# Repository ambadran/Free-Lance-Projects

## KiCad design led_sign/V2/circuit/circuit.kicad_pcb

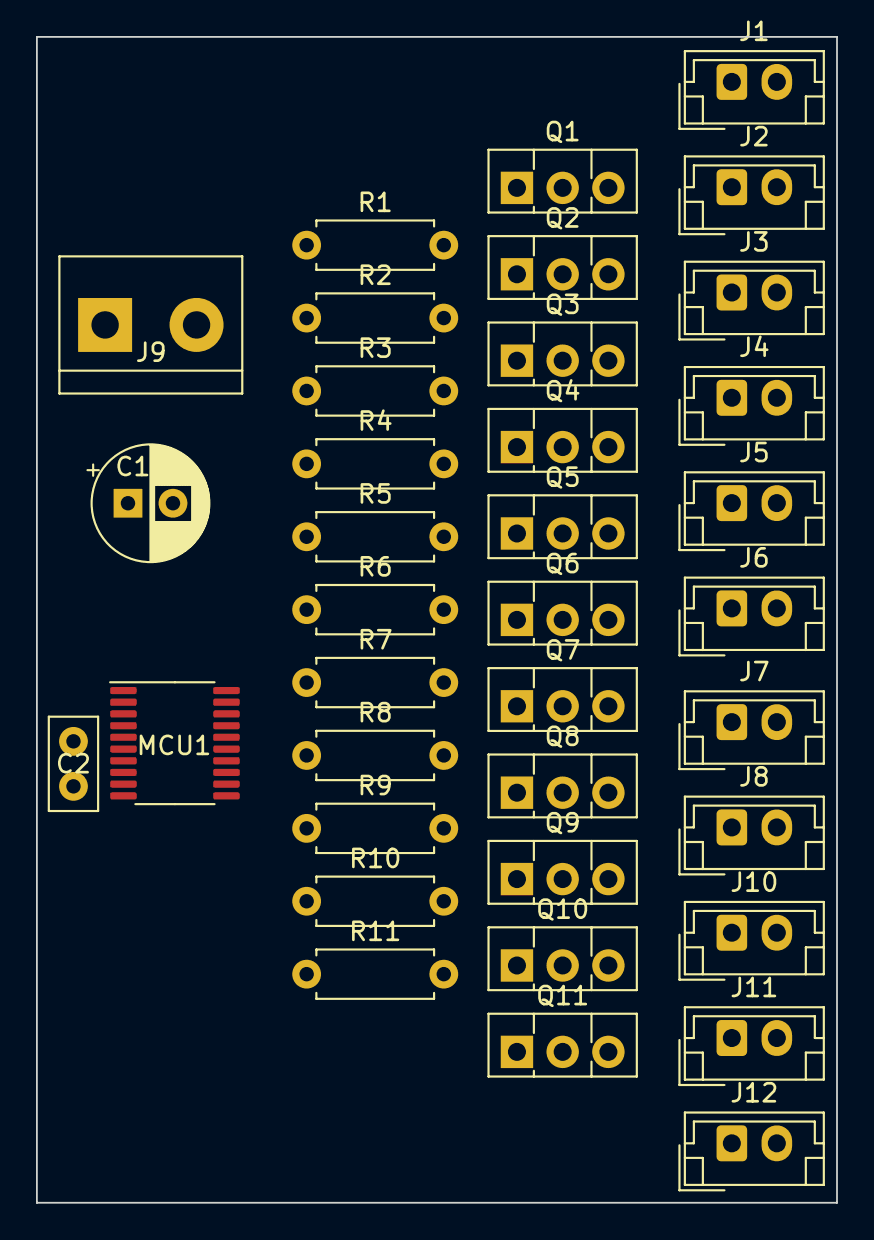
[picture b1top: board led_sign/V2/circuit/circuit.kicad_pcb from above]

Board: 2 copper layers, 44.5 x 64.8 mm, 37 parts (0 on the bottom side), 36 nets, no tracks yet.

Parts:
C1: 220uF; CP_Radial_D6.3mm_P2.50mm
C2: 10nF; C_Disc_D5.0mm_W2.5mm_P2.50mm
J1, J2, J3, J4, J5, J6, J7, J8, J10, J11, J12: JST2P; JST_EH_B2B-EH-A_1x02_P2.50mm_Vertical
J9: Terminal1x2; TerminalBlock_bornier-2_P5.08mm
MCU1: STC8G1k17; TSSOP-20_4.4x6.5mm_P0.65mm
Q1, Q2, Q3, Q4, Q5, Q6, Q7, Q8, Q9, Q10, Q11: Q_NPN_Darlington_BCE; TO-126-3_Vertical
R1, R2, R3, R4, R5, R6, R7, R8, R9, R10, R11: 330; R_Axial_DIN0207_L6.3mm_D2.5mm_P7.62mm_Horizontal

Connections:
+5V: C1.2, C2.1, MCU1.8, MCU1.9
+12V: J1.1, J2.1, J3.1, J4.1, J5.1, J6.1, J7.1, J8.1, J9.1, J10.1, J11.1, J12.1
GND: C1.1, C2.2, J9.2, MCU1.10, Q1.3 (E), Q2.3 (E), Q3.3 (E), Q4.3 (E), Q5.3 (E), Q6.3 (E), Q7.3 (E), Q8.3 (E), Q9.3 (E), Q10.3 (E), Q11.3 (E)
unnamed: J1.2, Q1.2 (C)
unnamed: J2.2, Q2.2 (C)
unnamed: J3.2, Q3.2 (C)
unnamed: J4.2, Q4.2 (C)
unnamed: J5.2, Q5.2 (C)
unnamed: J6.2, Q6.2 (C)
unnamed: J7.2, Q7.2 (C)
unnamed: J8.2, Q8.2 (C)
unnamed: J10.2, Q9.2 (C)
unnamed: J11.2, Q10.2 (C)
unnamed: J12.2, Q11.2 (C)
unnamed: Q1.1 (B), R1.2
unnamed: Q2.1 (B), R2.2
unnamed: Q3.1 (B), R3.2
unnamed: Q4.1 (B), R4.2
unnamed: Q5.1 (B), R5.2
unnamed: Q6.1 (B), R6.2
unnamed: Q7.1 (B), R7.2
unnamed: Q8.1 (B), R8.2
unnamed: Q9.1 (B), R9.2
unnamed: Q10.1 (B), R10.2
unnamed: Q11.1 (B), R11.2
Q1: MCU1.3, R1.1
Q2: MCU1.2, R2.1
Q3: MCU1.1, R3.1
Q4: MCU1.20, R4.1
Q5: MCU1.19, R5.1
Q6: MCU1.18, R6.1
Q7: MCU1.17, R7.1
Q8: MCU1.16, R8.1
Q9: MCU1.15, R9.1
Q10: MCU1.14, R10.1
Q11: MCU1.13, R11.1

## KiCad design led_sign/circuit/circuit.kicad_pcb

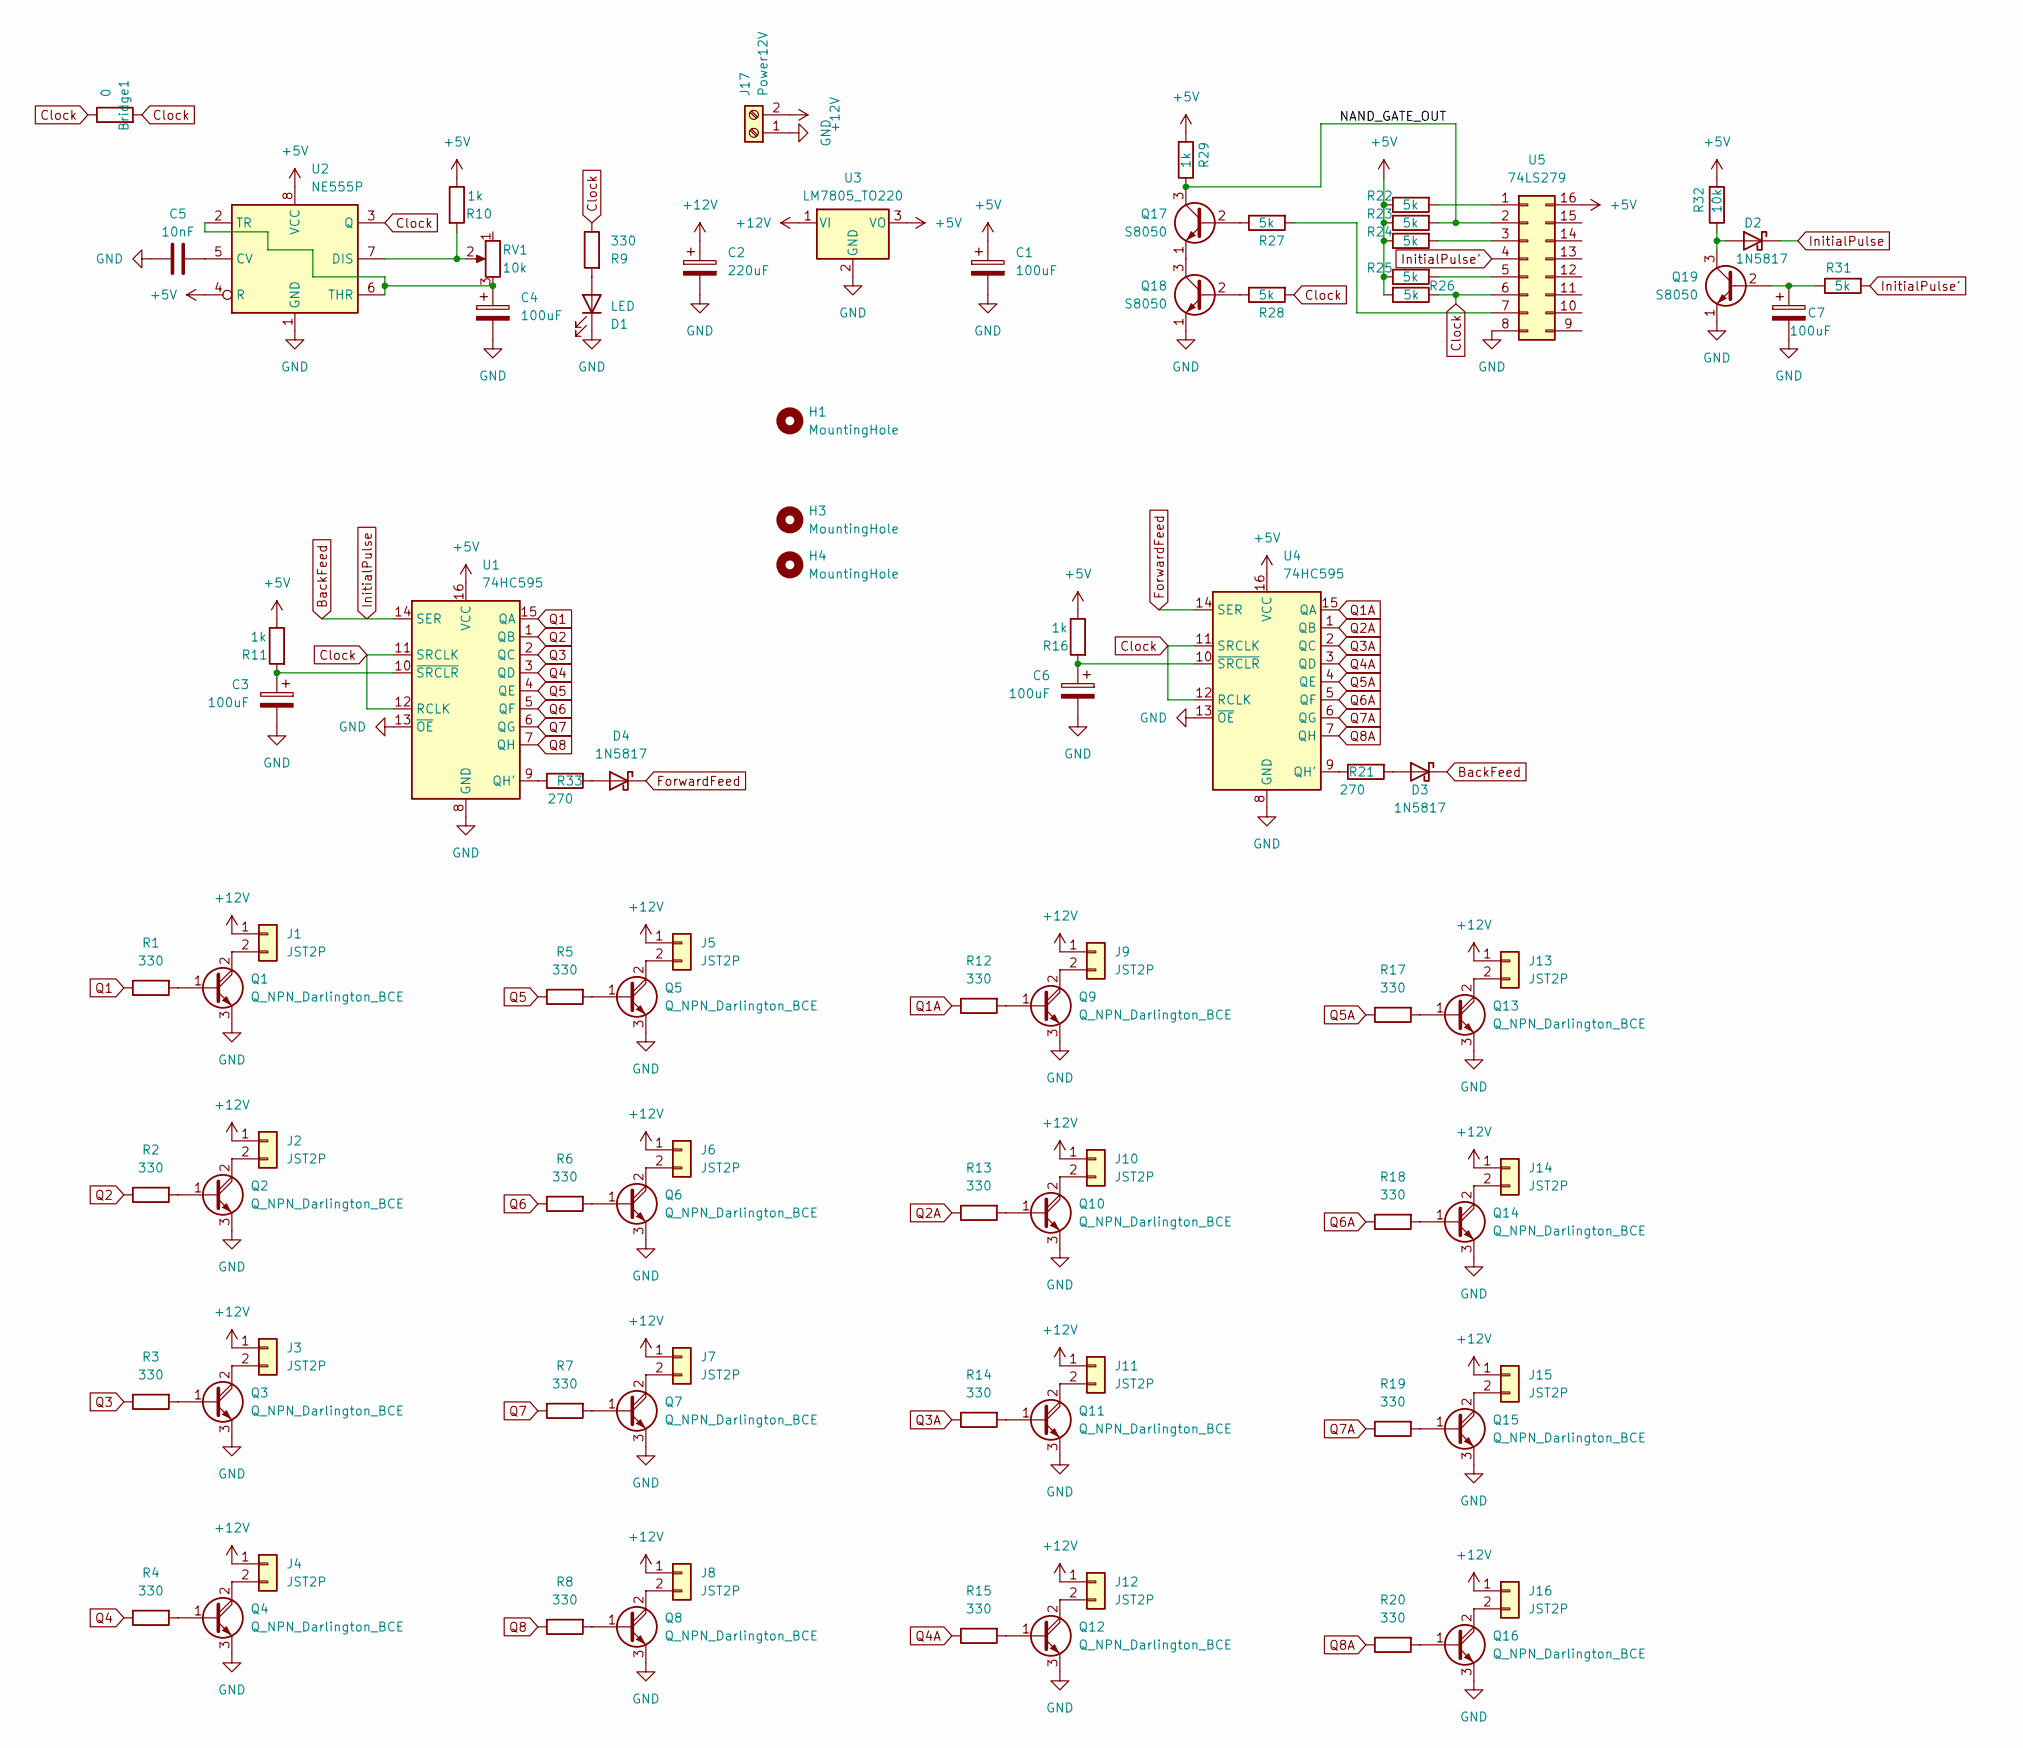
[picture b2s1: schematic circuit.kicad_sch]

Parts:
Bridge1: 0; R_Axial_DIN0207_L6.3mm_D2.5mm_P5.08mm_Vertical
C1, C3, C4, C6, C7: 100uF; CP_Radial_D5.0mm_P2.00mm
C2: 220uF; CP_Radial_D6.3mm_P2.50mm
C5: 10nF; C_Disc_D5.0mm_W2.5mm_P2.50mm
D1: LED; LED_D5.0mm
D2, D3, D4: 1N5817; D_DO-41_SOD81_P10.16mm_Horizontal
H1, H3, H4: MountingHole; MountingHole_3mm_Pad_TopBottom
J1, J2, J3, J4, J5, J6, J7, J8, J9, J10, J11, J12, J13, J14, J15, J16: JST2P; JST_EH_B2B-EH-A_1x02_P2.50mm_Vertical
J17: Power12V; TerminalBlock_bornier-2_P5.08mm
Q1, Q2, Q3, Q4, Q5, Q6, Q7, Q8, Q9, Q10, Q11, Q12, Q13, Q14, Q15, Q16: Q_NPN_Darlington_BCE; TO-126-3_Vertical
Q17, Q18, Q19: S8050; TO-92_Inline_Wide
R1, R2, R3, R4, R5, R6, R7, R8, R9, R12, R13, R14, R15, R17, R18, R19, R20: 330; R_Axial_DIN0207_L6.3mm_D2.5mm_P7.62mm_Horizontal
R10, R11, R16, R29: 1k; R_Axial_DIN0207_L6.3mm_D2.5mm_P7.62mm_Horizontal
R21, R33: 270; R_Axial_DIN0207_L6.3mm_D2.5mm_P7.62mm_Horizontal
R22, R23, R24, R25, R26, R27, R28, R31: 5k; R_Axial_DIN0207_L6.3mm_D2.5mm_P7.62mm_Horizontal
R32: 10k; R_Axial_DIN0207_L6.3mm_D2.5mm_P7.62mm_Horizontal
RV1: 10k; PinHeader_1x03_P2.54mm_Vertical
U1: 74HC595; DIP-16_W7.62mm_LongPads
U2: NE555P; DIP-8_W7.62mm
U3: LM7805_TO220; TO-220-3_Vertical
U4: 74HC595; DIP-16_W7.62mm_Socket_LongPads
U5: 74LS279; DIP-16_W7.62mm_Socket_LongPads

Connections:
+5V: C1.1, R10.1, R11.1, R16.1, R22.1, R23.1, R24.1, R25.1, R26.2, R29.2, R32.2, U1.16 (VCC), U2.4 (R), U2.8 (VCC), U3.3 (VO), U4.16 (VCC), U5.16
+12V: C2.1, J1.1, J2.1, J3.1, J4.1, J5.1, J6.1, J7.1, J8.1, J9.1, J10.1, J11.1, J12.1, J13.1, J14.1, J15.1, J16.1, J17.2, U3.1 (VI)
/NAND_GATE_OUT: Q17.3 (C), R23.2, R29.1, U5.2
BackFeed: D2.1 (K), D3.1 (K), U1.14 (SER)
Clock: Bridge1.1, Bridge1.2, R9.1, R26.1, R28.2, U1.11 (SRCLK), U1.12 (RCLK), U2.3 (Q), U4.11 (SRCLK), U4.12 (RCLK), U5.6
ForwardFeed: D4.1 (K), U4.14 (SER)
GND: C1.2, C2.2, C3.2, C4.2, C5.1, C6.2, C7.2, D1.1 (K), J17.1, Q1.3 (E), Q2.3 (E), Q3.3 (E), Q4.3 (E), Q5.3 (E), Q6.3 (E), Q7.3 (E), Q8.3 (E), Q9.3 (E), Q10.3 (E), Q11.3 (E), Q12.3 (E), Q13.3 (E), Q14.3 (E), Q15.3 (E), Q16.3 (E), Q18.1 (E), Q19.1 (E), U1.8 (GND), U1.13 (~OE), U2.1 (GND), U3.2 (GND), U4.8 (GND), U4.13 (~OE), U5.8
InitialPulse': R31.2, U5.4
unnamed: D1.2 (A), R9.2
unnamed: D2.2 (A), Q19.3 (C), R32.1
unnamed: D3.2 (A), R21.2
unnamed: D4.2 (A), R33.2
unnamed: J1.2, Q1.2 (C)
unnamed: J2.2, Q2.2 (C)
unnamed: J3.2, Q3.2 (C)
unnamed: J4.2, Q4.2 (C)
unnamed: J5.2, Q5.2 (C)
unnamed: J6.2, Q6.2 (C)
unnamed: J7.2, Q7.2 (C)
unnamed: J8.2, Q8.2 (C)
unnamed: J9.2, Q9.2 (C)
unnamed: J10.2, Q10.2 (C)
unnamed: J11.2, Q11.2 (C)
unnamed: J12.2, Q12.2 (C)
unnamed: J13.2, Q13.2 (C)
unnamed: J14.2, Q14.2 (C)
unnamed: J15.2, Q15.2 (C)
unnamed: J16.2, Q16.2 (C)
unnamed: Q1.1 (B), R1.2
unnamed: Q2.1 (B), R2.2
unnamed: Q3.1 (B), R3.2
unnamed: Q4.1 (B), R4.2
unnamed: Q5.1 (B), R5.2
unnamed: Q6.1 (B), R6.2
unnamed: Q7.1 (B), R7.2
unnamed: Q8.1 (B), R8.2
unnamed: Q9.1 (B), R12.2
unnamed: Q10.1 (B), R13.2
unnamed: Q11.1 (B), R14.2
unnamed: Q12.1 (B), R15.2
unnamed: Q13.1 (B), R17.2
unnamed: Q14.1 (B), R18.2
unnamed: Q15.1 (B), R19.2
unnamed: Q16.1 (B), R20.2
unnamed: Q17.2 (B), R27.1
unnamed: Q17.1 (E), Q18.3 (C)
unnamed: Q18.2 (B), R28.1
unnamed: C7.1, Q19.2 (B), R31.1
unnamed: R33.1, U1.9 (QH')
unnamed: C3.1, R11.2, U1.10 (~SRCLR)
unnamed: C5.2, U2.5 (CV)
unnamed: R10.2, RV1.2, U2.7 (DIS)
unnamed: C4.1, RV1.3, U2.2 (TR), U2.6 (THR)
unnamed: R21.1, U4.9 (QH')
unnamed: C6.1, R16.2, U4.10 (~SRCLR)
unnamed: R22.2, U5.1
unnamed: R24.2, U5.3
unnamed: R25.2, U5.5
unnamed: R27.2, U5.7
Q1: R1.1, U1.15 (QA)
Q1A: R12.1, U4.15 (QA)
Q2: R2.1, U1.1 (QB)
Q2A: R13.1, U4.1 (QB)
Q3: R3.1, U1.2 (QC)
Q3A: R14.1, U4.2 (QC)
Q4: R4.1, U1.3 (QD)
Q4A: R15.1, U4.3 (QD)
Q5: R5.1, U1.4 (QE)
Q5A: R17.1, U4.4 (QE)
Q6: R6.1, U1.5 (QF)
Q6A: R18.1, U4.5 (QF)
Q7: R7.1, U1.6 (QG)
Q7A: R19.1, U4.6 (QG)
Q8: R8.1, U1.7 (QH)
Q8A: R20.1, U4.7 (QH)

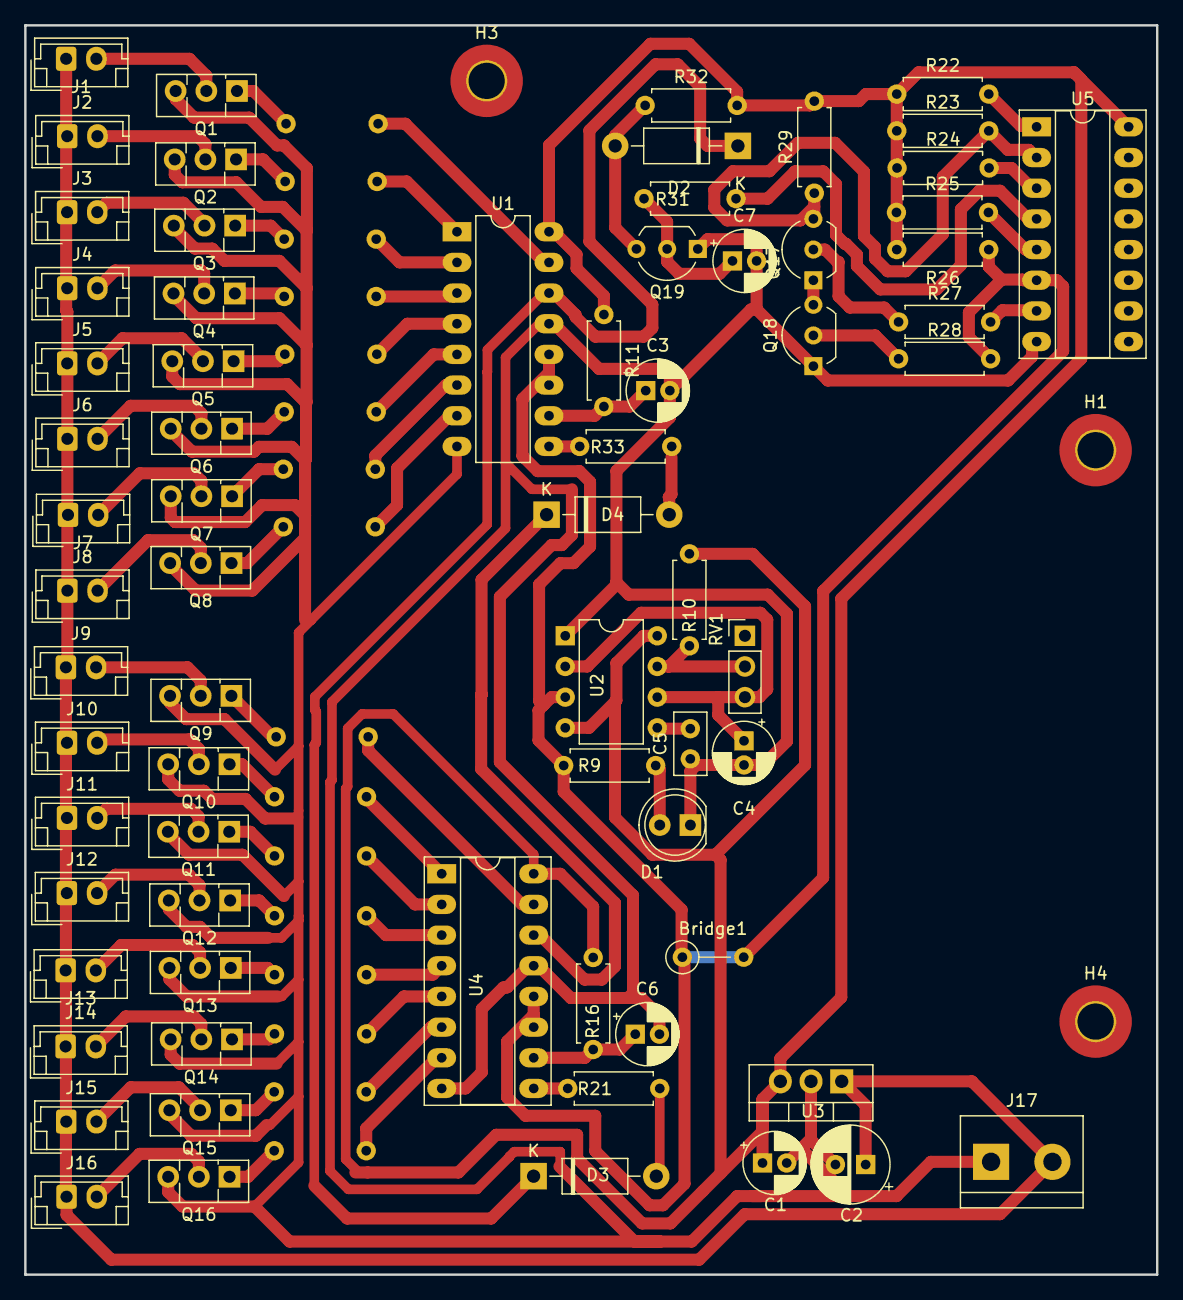
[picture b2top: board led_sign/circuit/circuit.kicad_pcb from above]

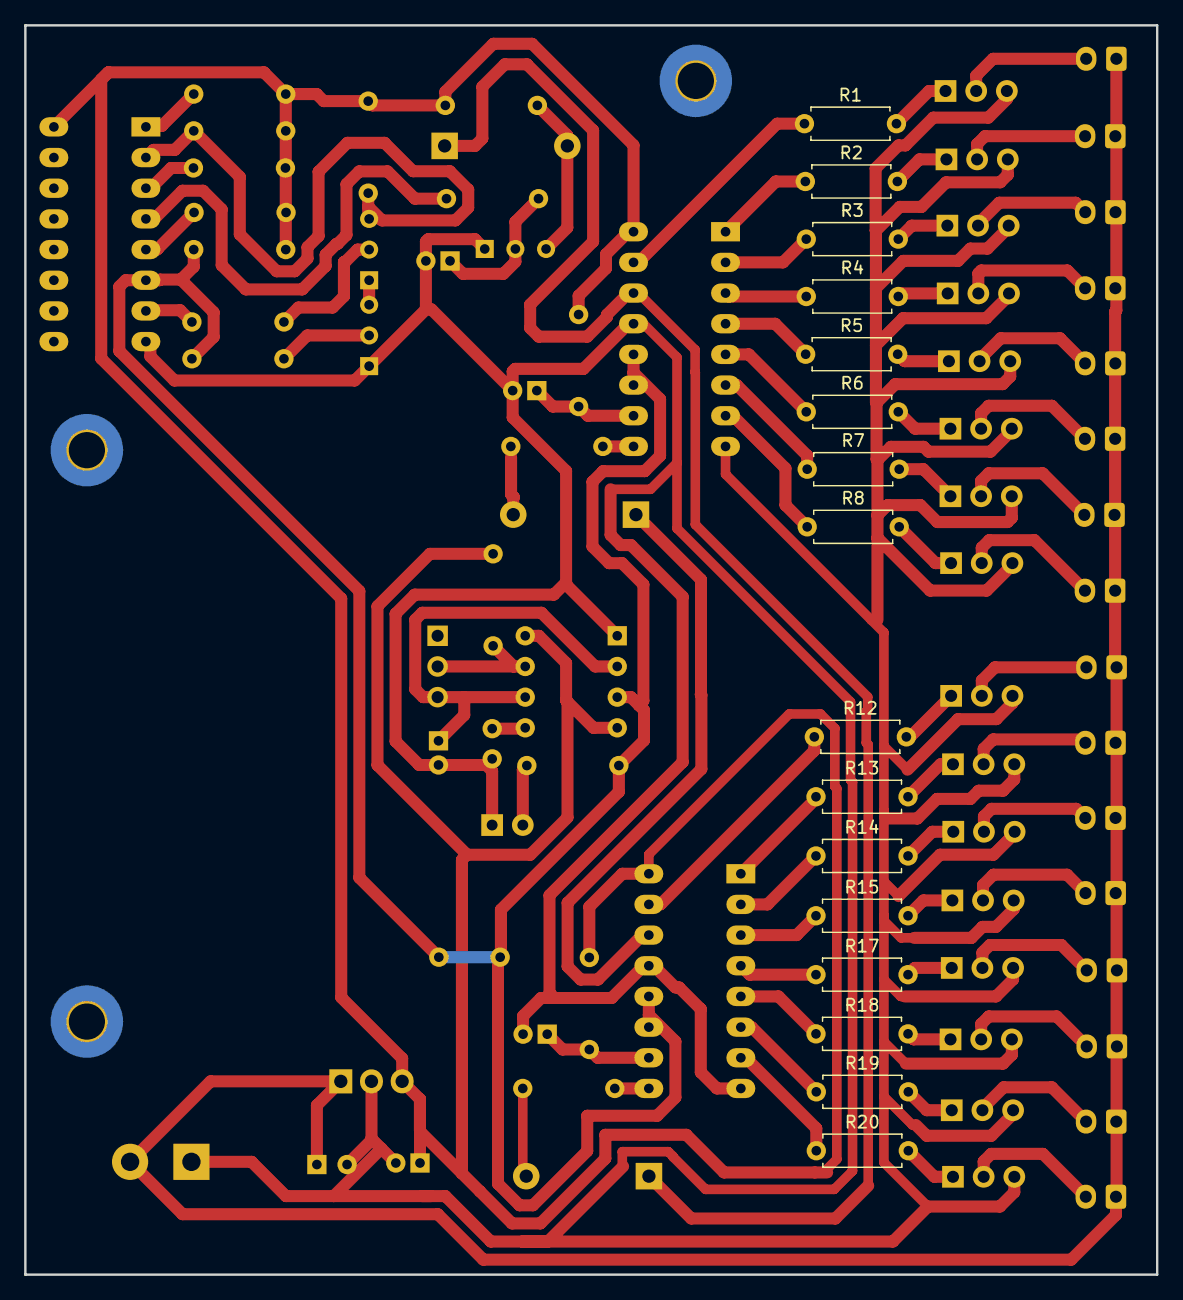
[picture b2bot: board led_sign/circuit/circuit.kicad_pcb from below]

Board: 2 copper layers, 93.7 x 103.5 mm, 89 parts (16 on the bottom side), 75 nets.

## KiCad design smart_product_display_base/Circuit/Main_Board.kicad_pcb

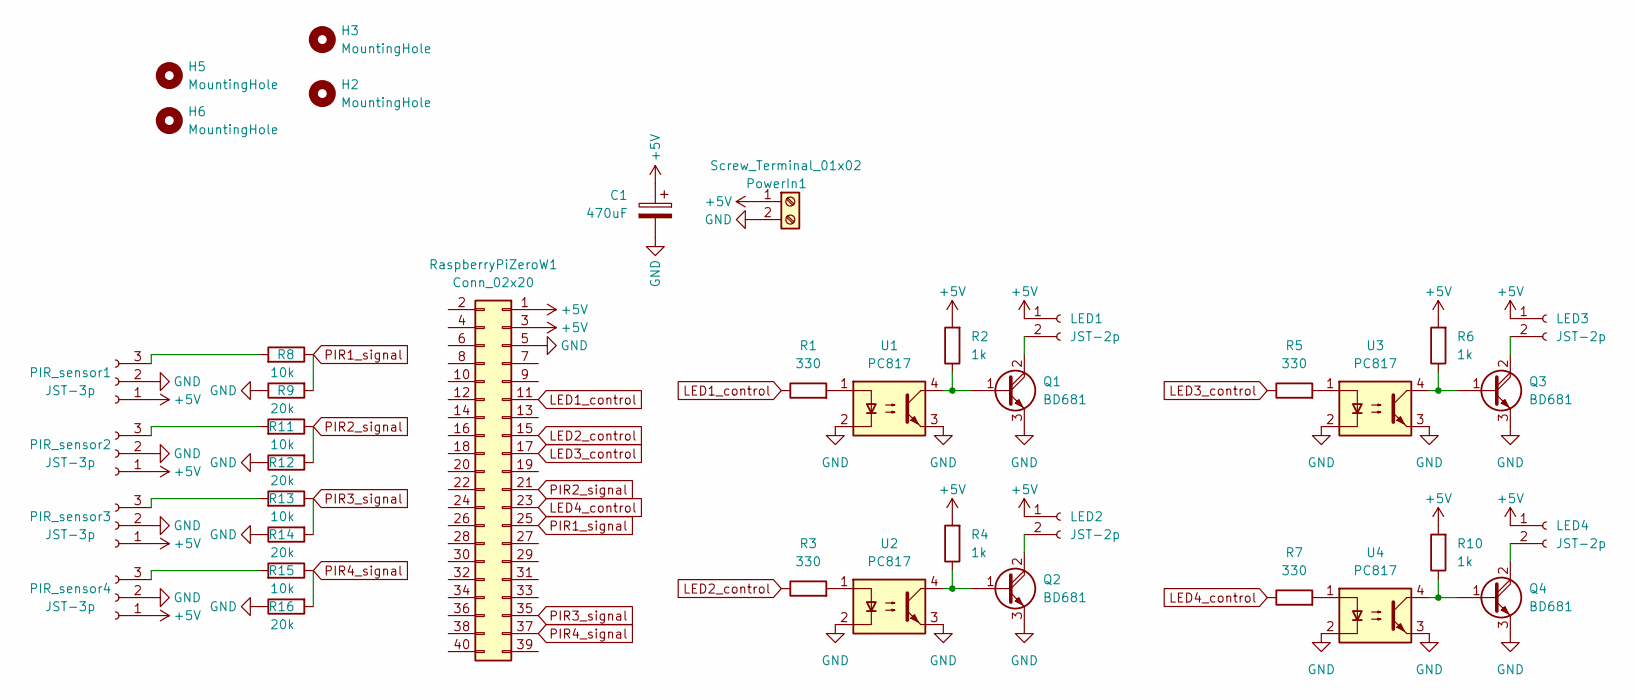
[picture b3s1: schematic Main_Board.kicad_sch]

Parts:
C1: 470uF; CP_Radial_D8.0mm_P3.50mm
H2, H3: MountingHole; MountingHole_4mm_Pad_TopOnly
H5, H6: MountingHole; MountingHole_2.5mm_Pad_TopOnly
LED1, LED2, LED3, LED4: JST-2p; JST_EH_B2B-EH-A_1x02_P2.50mm_Vertical
PIR_sensor1, PIR_sensor2, PIR_sensor3, PIR_sensor4: JST-3p; JST_EH_B3B-EH-A_1x03_P2.50mm_Vertical
PowerIn1: Screw_Terminal_01x02; TerminalBlock_bornier-2_P5.08mm
Q1, Q2, Q3, Q4: BD681; TO-126-3_Vertical
R1, R3, R5, R7: 330; R_Axial_DIN0207_L6.3mm_D2.5mm_P7.62mm_Horizontal
R2, R4, R6, R10: 1k; R_Axial_DIN0207_L6.3mm_D2.5mm_P7.62mm_Horizontal
R8, R11, R13, R15: 10k; R_Axial_DIN0207_L6.3mm_D2.5mm_P7.62mm_Horizontal
R9, R12, R14, R16: 20k; R_Axial_DIN0207_L6.3mm_D2.5mm_P7.62mm_Horizontal
RaspberryPiZeroW1: Conn_02x20; PinSocket_2x20_P2.54mm_Vertical
U1, U2, U3, U4: PC817; DIP-4_W7.62mm

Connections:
+5V: C1.1, LED1.1, LED2.1, LED3.1, LED4.1, PIR_sensor1.1, PIR_sensor2.1, PIR_sensor3.1, PIR_sensor4.1, PowerIn1.1, R2.2, R4.2, R6.2, R10.2, RaspberryPiZeroW1.1, RaspberryPiZeroW1.3
GND: C1.2, PIR_sensor1.2, PIR_sensor2.2, PIR_sensor3.2, PIR_sensor4.2, PowerIn1.2, Q1.3 (E), Q2.3 (E), Q3.3 (E), Q4.3 (E), R9.1, R12.1, R14.1, R16.1, RaspberryPiZeroW1.5, U1.2, U1.3, U2.2, U2.3, U3.2, U3.3, U4.2, U4.3
LED1_control: R1.1, RaspberryPiZeroW1.11
LED2_control: R3.1, RaspberryPiZeroW1.15
LED3_control: R5.1, RaspberryPiZeroW1.17
LED4_control: R7.1, RaspberryPiZeroW1.23
unnamed: LED1.2, Q1.2 (C)
unnamed: LED2.2, Q2.2 (C)
unnamed: LED3.2, Q3.2 (C)
unnamed: LED4.2, Q4.2 (C)
unnamed: PIR_sensor1.3, R8.2
unnamed: PIR_sensor2.3, R11.2
unnamed: PIR_sensor3.3, R13.2
unnamed: PIR_sensor4.3, R15.2
unnamed: Q1.1 (B), R2.1, U1.4
unnamed: Q2.1 (B), R4.1, U2.4
unnamed: Q3.1 (B), R6.1, U3.4
unnamed: Q4.1 (B), R10.1, U4.4
unnamed: R1.2, U1.1
unnamed: R3.2, U2.1
unnamed: R5.2, U3.1
unnamed: R7.2, U4.1
PIR1_signal: R8.1, R9.2, RaspberryPiZeroW1.25
PIR2_signal: R11.1, R12.2, RaspberryPiZeroW1.21
PIR3_signal: R13.1, R14.2, RaspberryPiZeroW1.35
PIR4_signal: R15.1, R16.2, RaspberryPiZeroW1.37

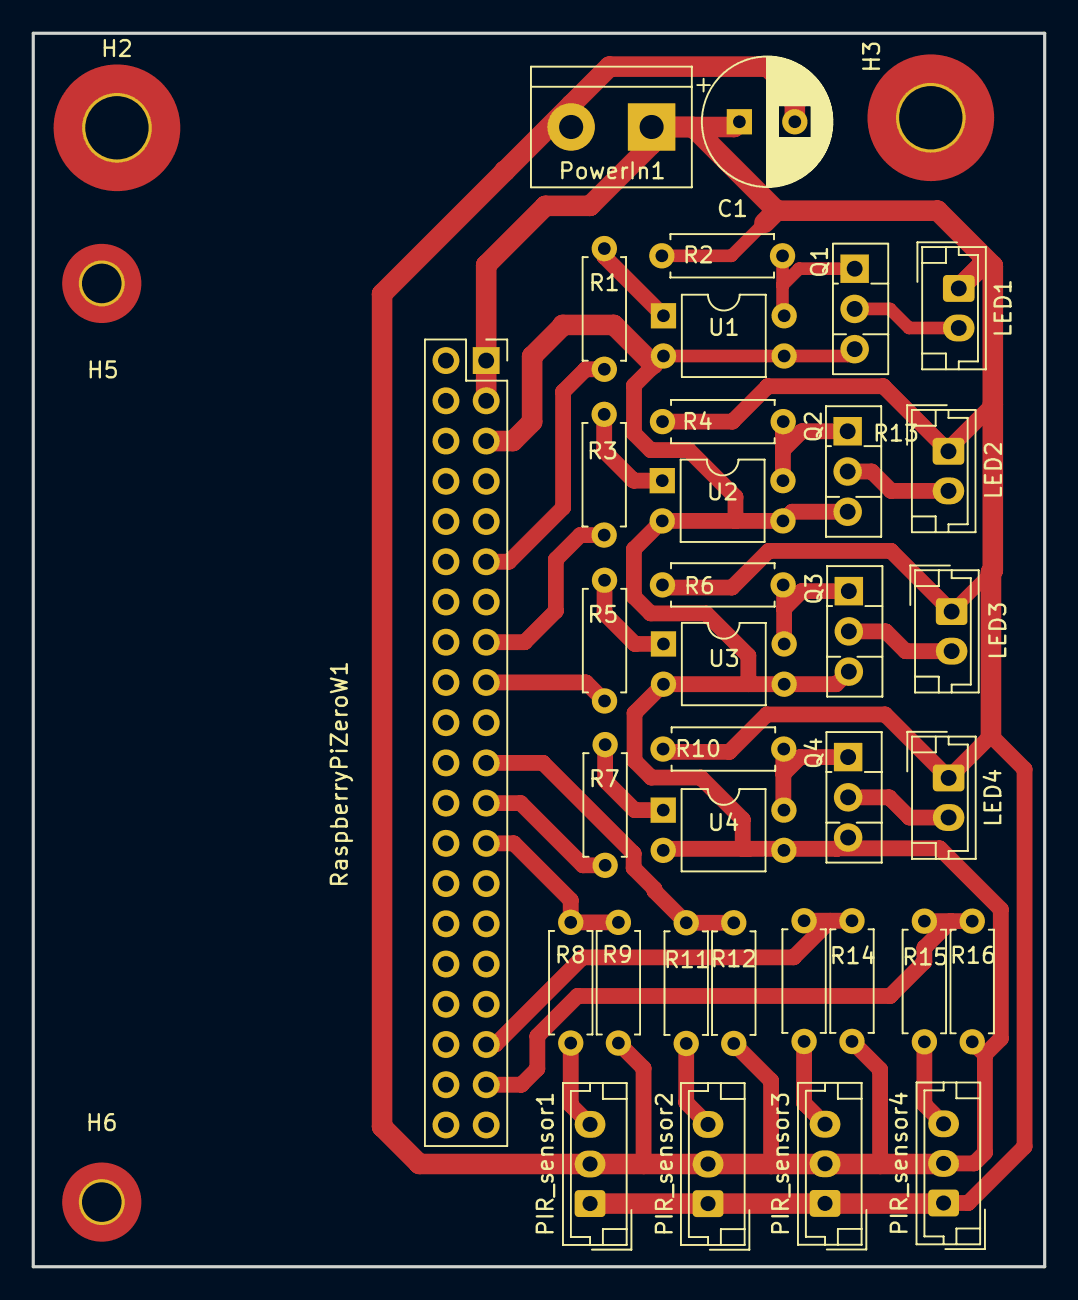
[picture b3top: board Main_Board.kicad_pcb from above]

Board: 2 copper layers, 63.9 x 77.9 mm, 39 parts (0 on the bottom side), 26 nets.

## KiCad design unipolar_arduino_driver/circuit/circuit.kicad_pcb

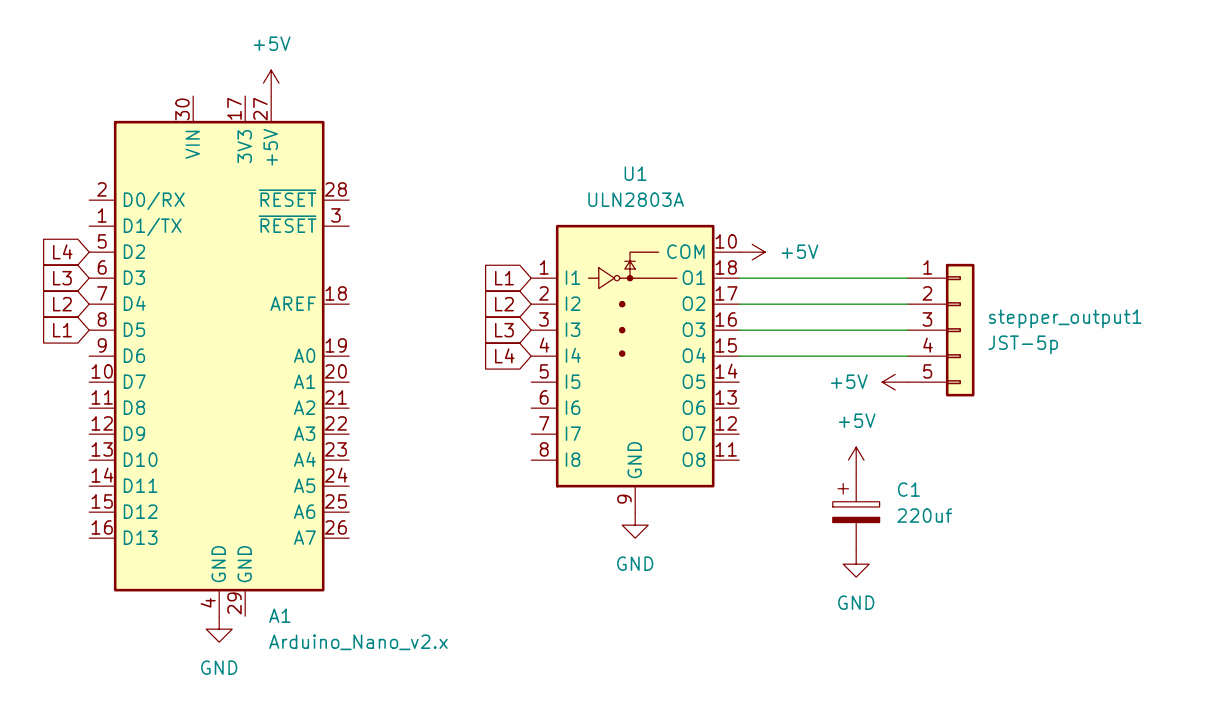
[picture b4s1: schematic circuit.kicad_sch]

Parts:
A1: Arduino_Nano_v2.x; Arduino_Nano
C1: 220uf; CP_Radial_D6.3mm_P2.50mm
U1: ULN2803A; DIP-18_W7.62mm_Socket_LongPads
stepper_output1: JST-5p; JST_EH_B5B-EH-A_1x05_P2.50mm_Vertical

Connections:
+5V: A1.27 (+5V), C1.1, U1.10 (COM), stepper_output1.5
GND: A1.4 (GND), C1.2, U1.9 (GND)
L1: A1.8 (D5), U1.1 (I1)
L2: A1.7 (D4), U1.2 (I2)
L3: A1.6 (D3), U1.3 (I3)
L4: A1.5 (D2), U1.4 (I4)
unnamed: U1.18 (O1), stepper_output1.1
unnamed: U1.17 (O2), stepper_output1.2
unnamed: U1.16 (O3), stepper_output1.3
unnamed: U1.15 (O4), stepper_output1.4

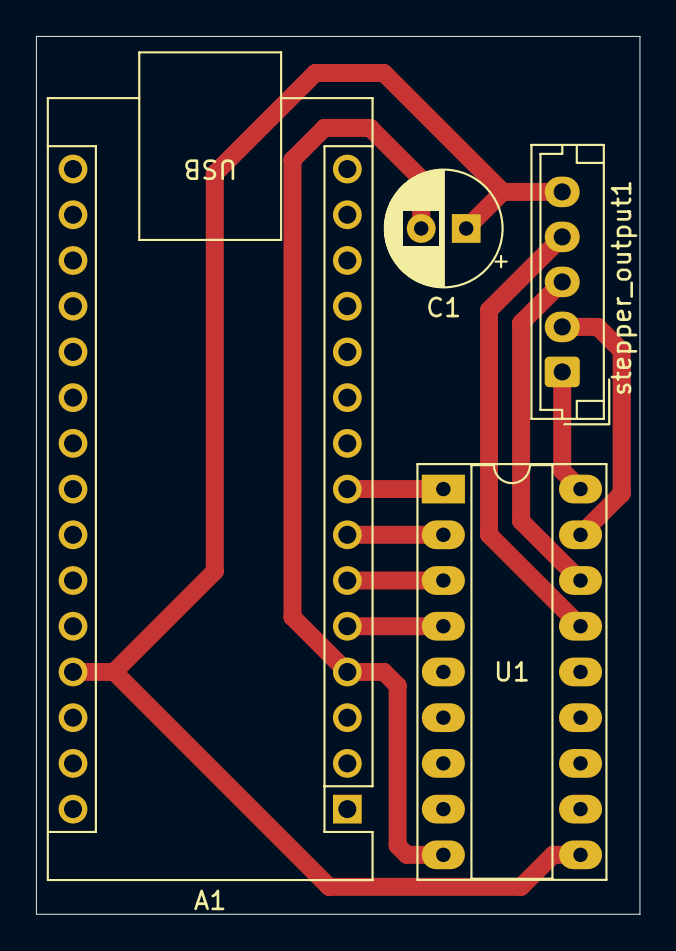
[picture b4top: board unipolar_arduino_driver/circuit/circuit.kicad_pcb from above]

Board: 2 copper layers, 33.5 x 48.8 mm, 4 parts (0 on the bottom side), 10 nets.
